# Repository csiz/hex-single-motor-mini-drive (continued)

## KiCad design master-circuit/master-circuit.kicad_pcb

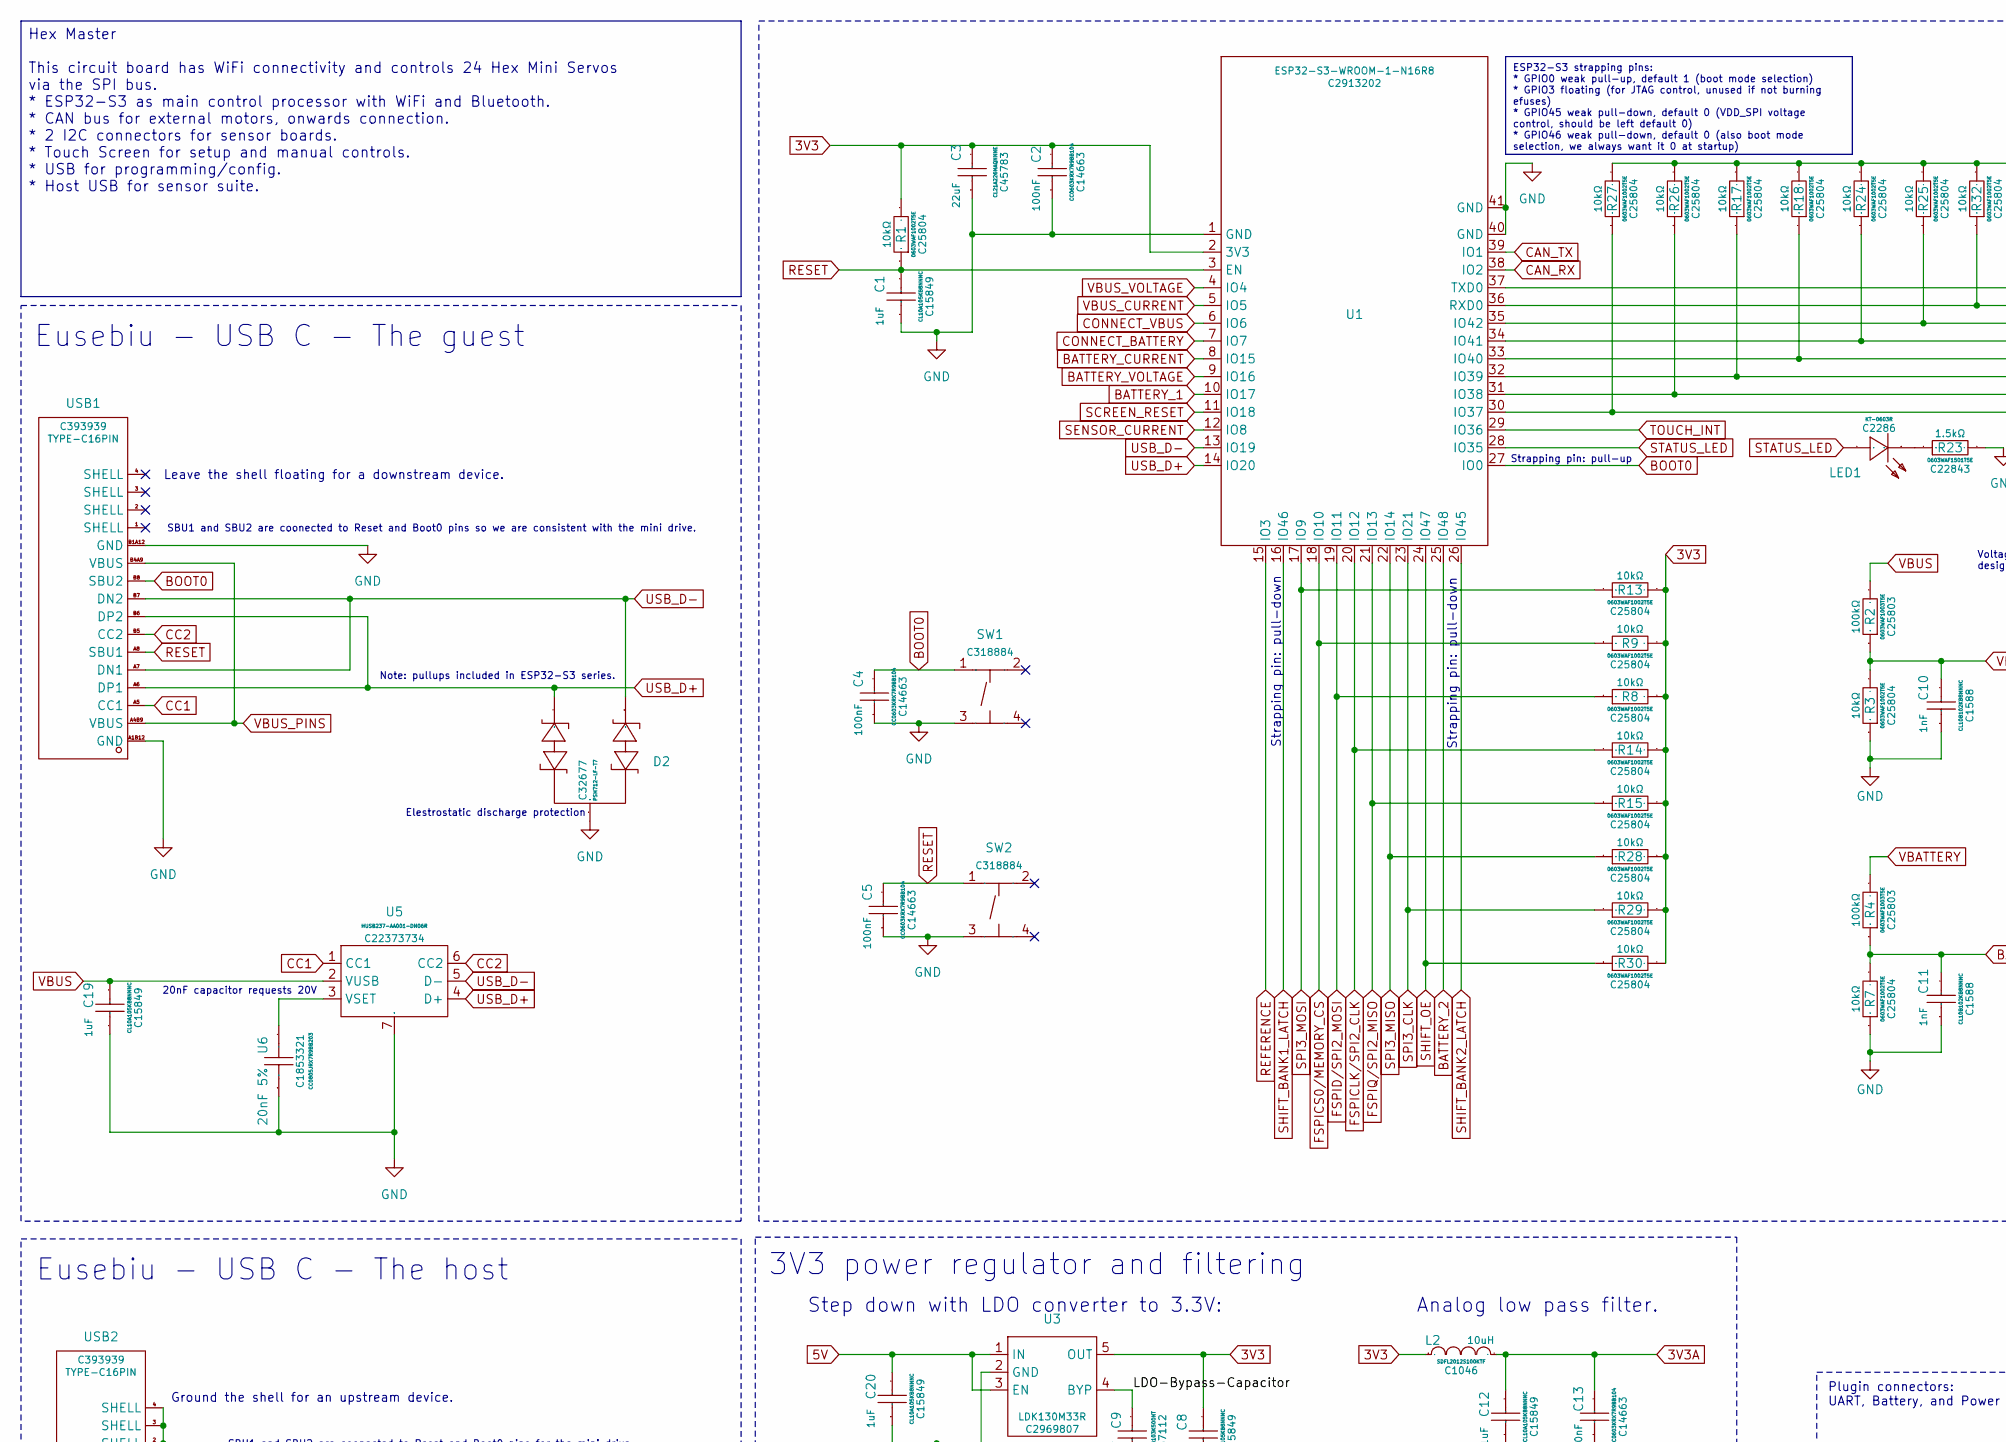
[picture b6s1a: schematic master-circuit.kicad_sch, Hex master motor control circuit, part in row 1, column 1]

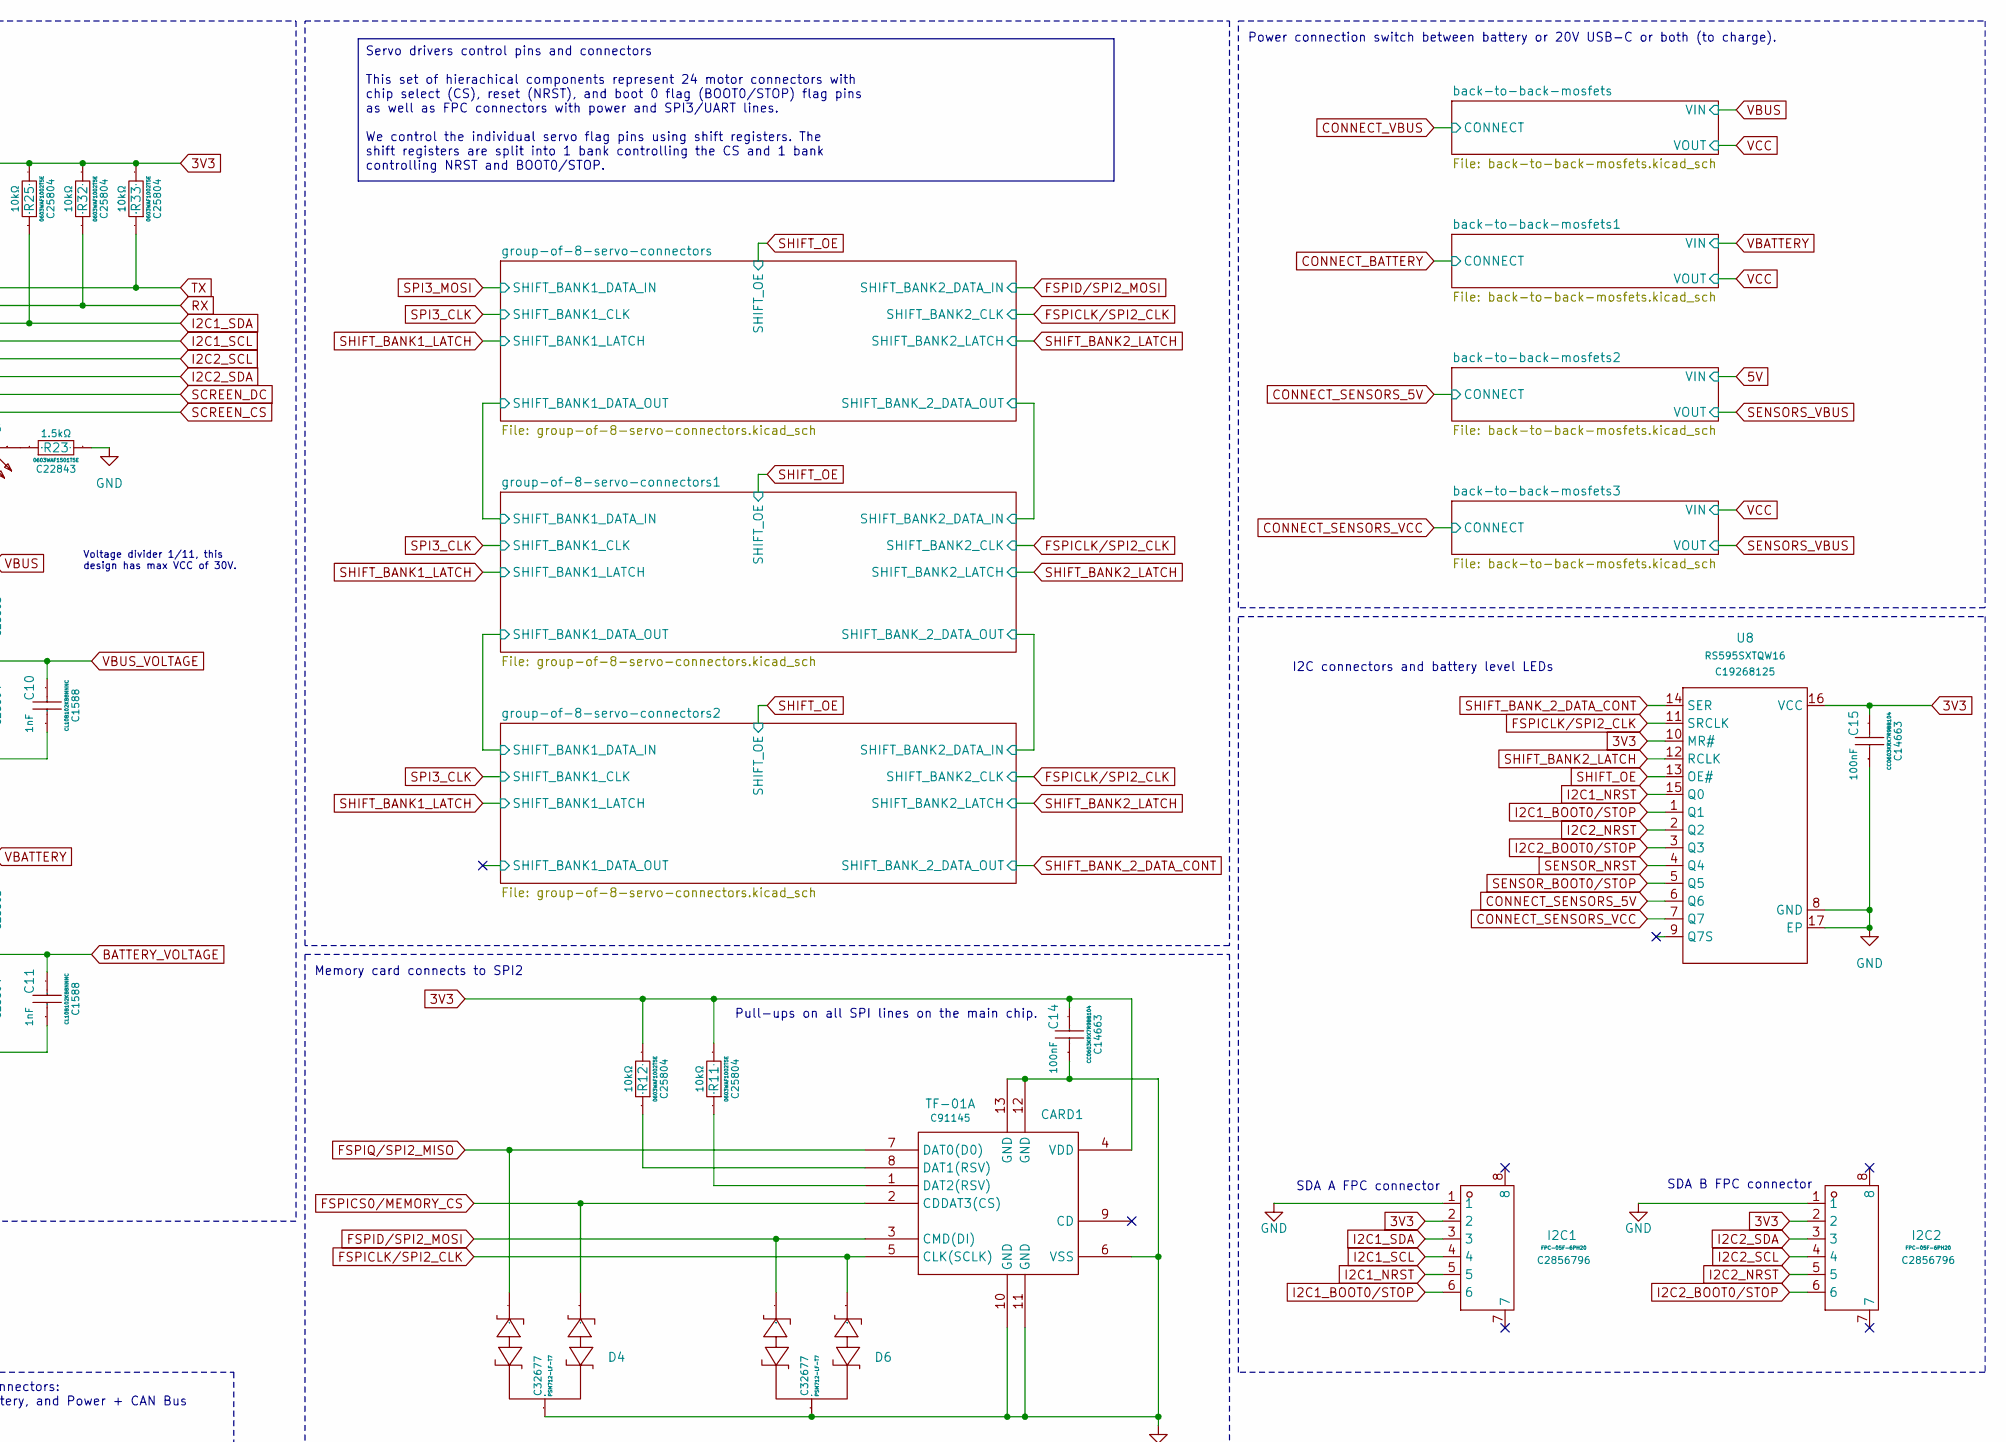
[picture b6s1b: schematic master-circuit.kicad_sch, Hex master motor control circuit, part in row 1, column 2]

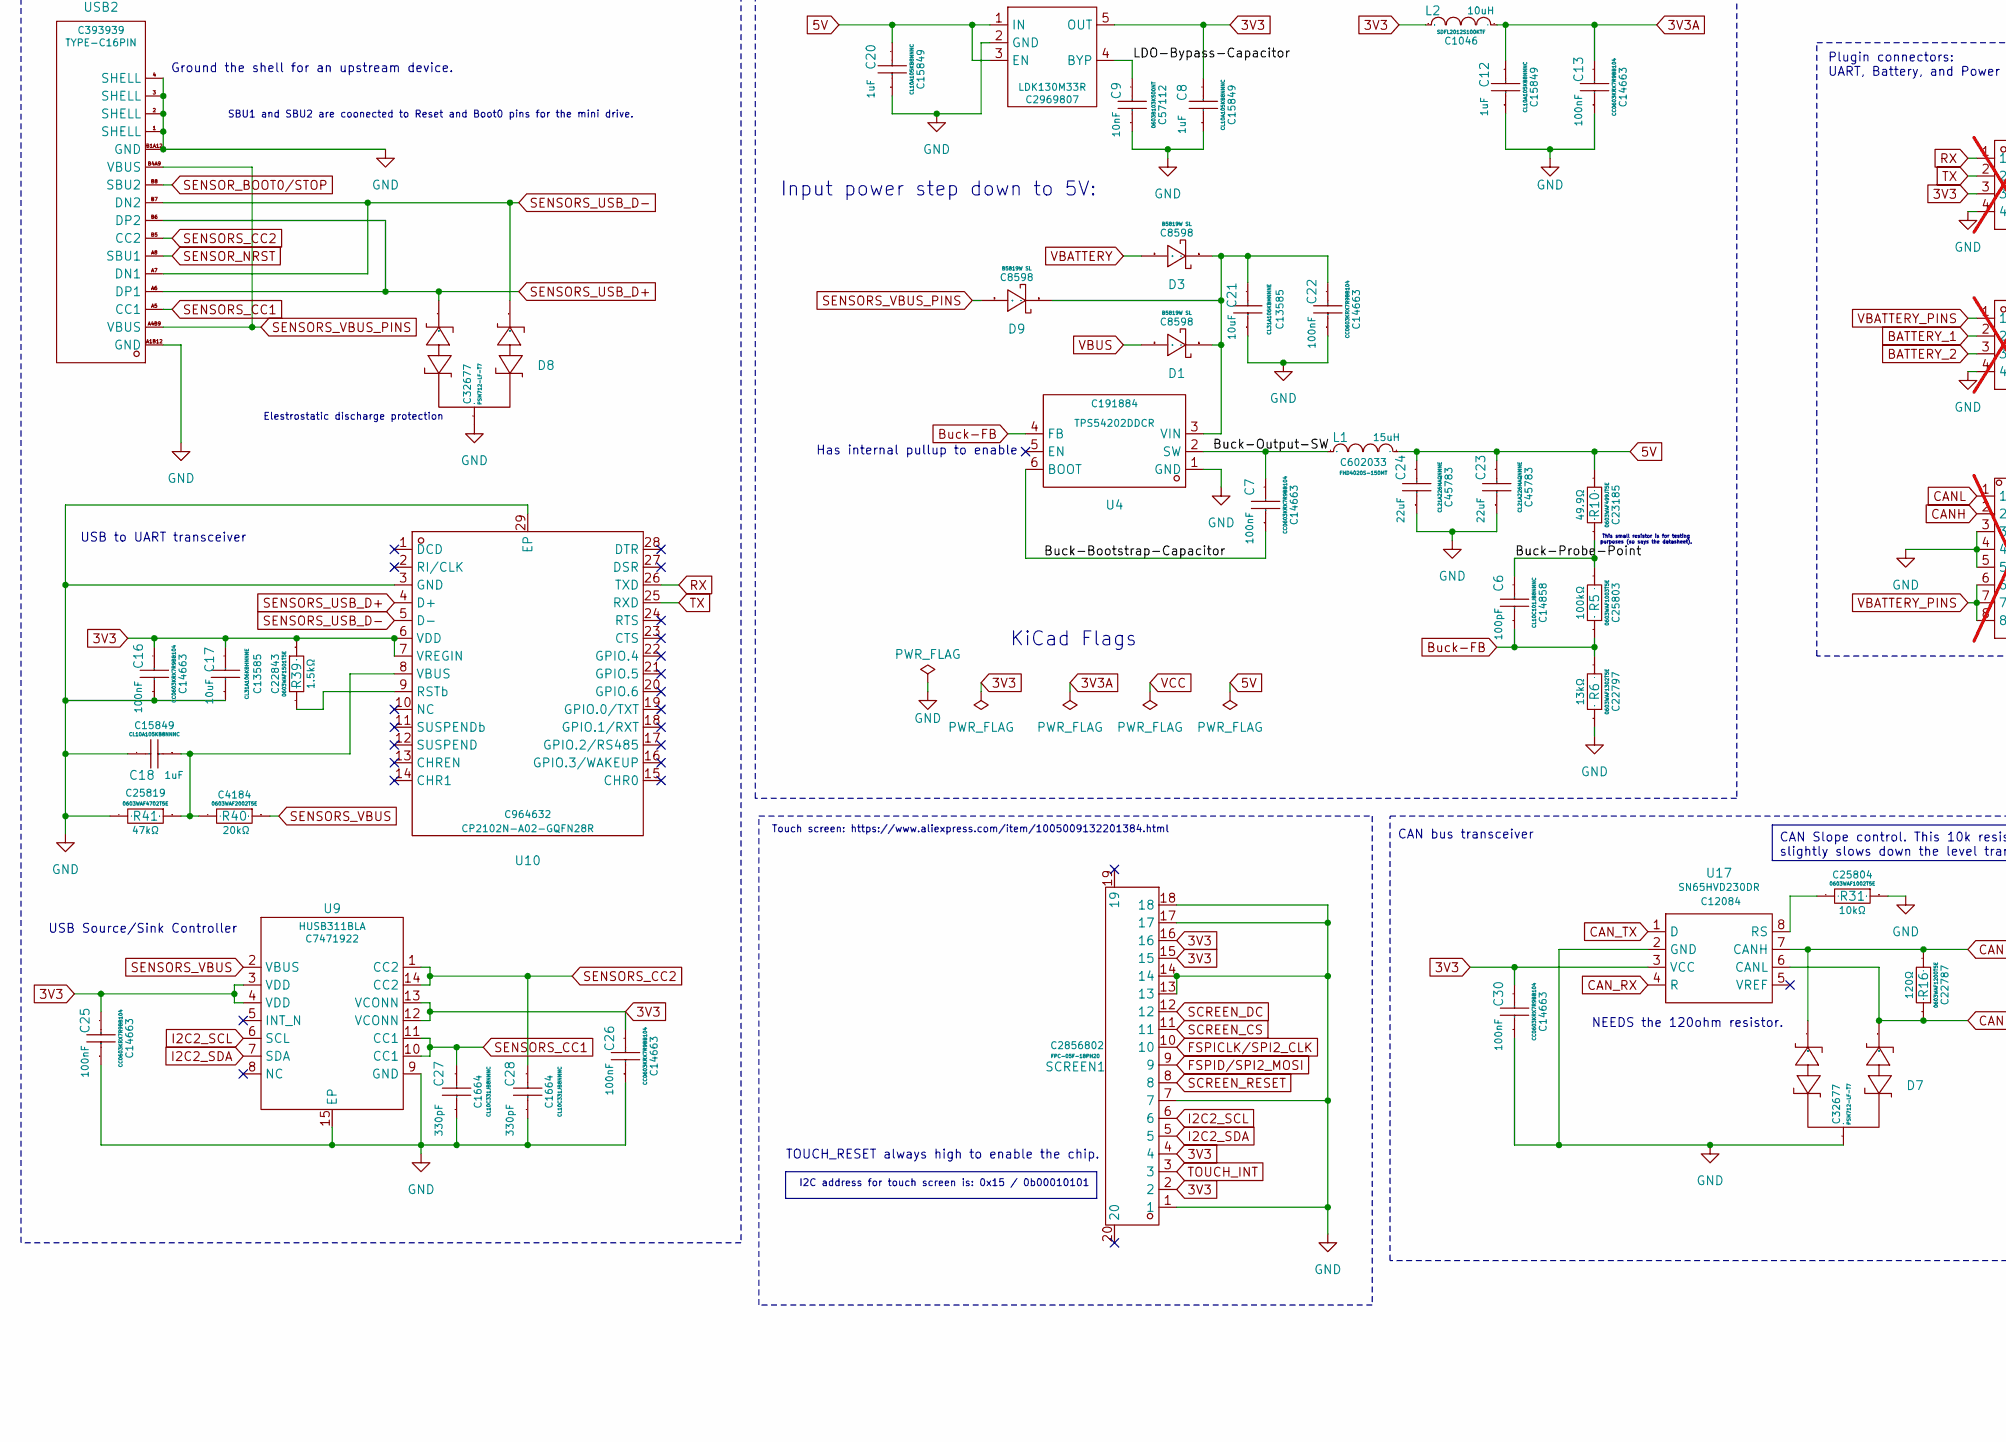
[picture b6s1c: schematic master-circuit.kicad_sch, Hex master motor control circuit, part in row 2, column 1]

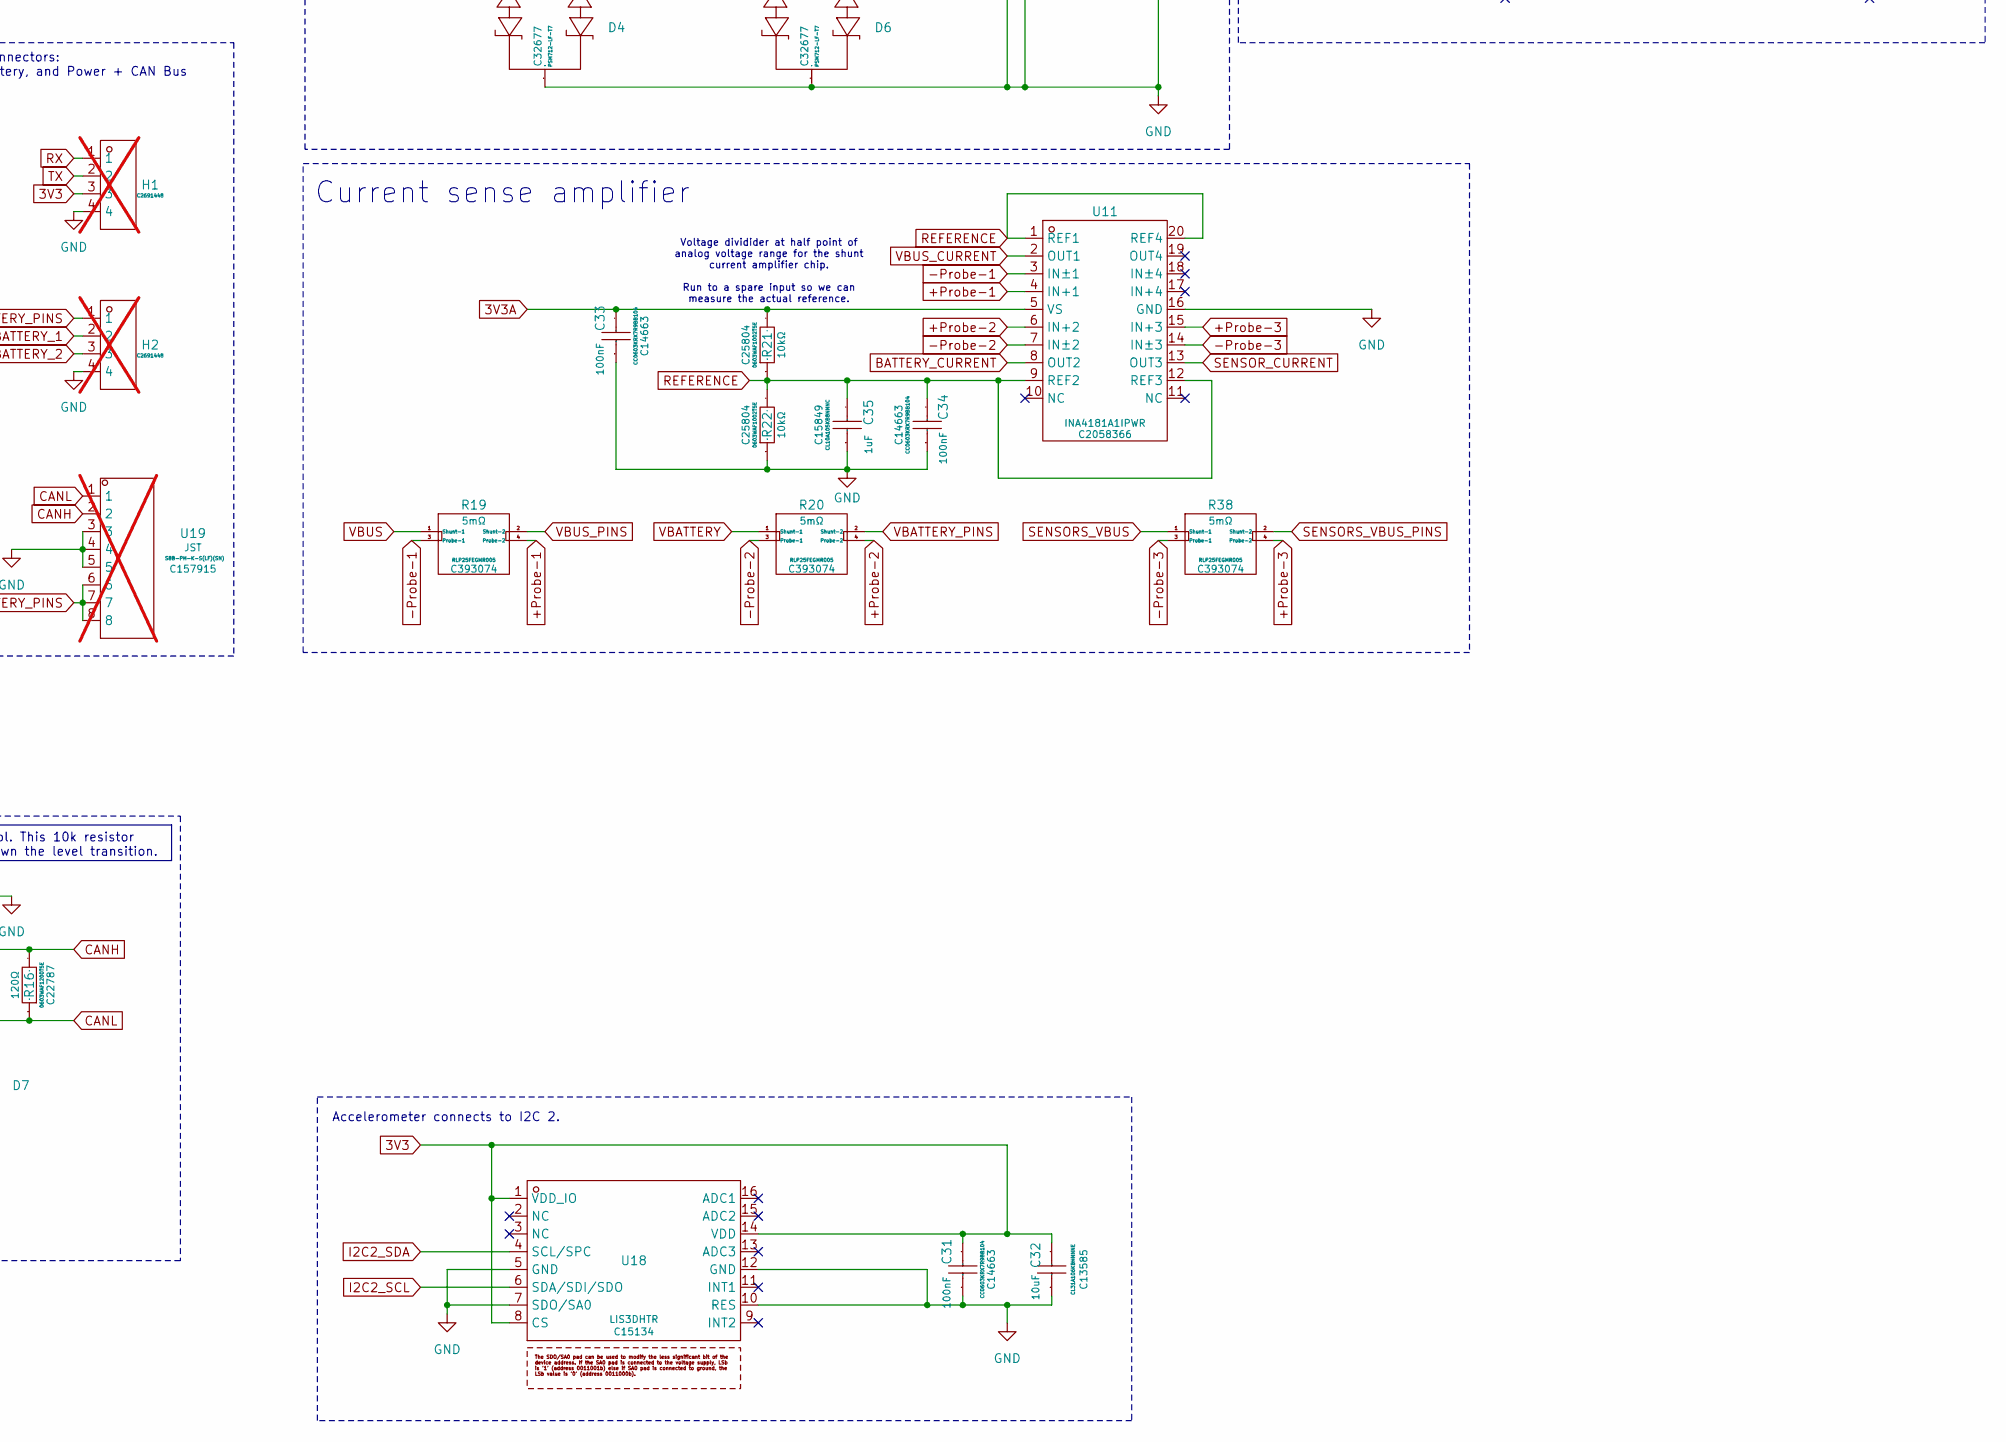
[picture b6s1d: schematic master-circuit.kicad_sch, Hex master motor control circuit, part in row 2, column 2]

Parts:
C1, C8, C12, C18, C19, C20, C35: 1uF; C0603; Manufacturer Part CL10A105KB8NNNC; LCSC Part Name 1uF ±10% 50V
C2, C4, C5, C7, C13, C14, C15, C16, C22, C25, C26, C30, C31, C33, C34: 100nF; C0603; Manufacturer Part CC0603KRX7R9BB104; LCSC Part Name 100nF ±10% 50V
C3, C23, C24: 22uF; C0805; Manufacturer Part CL21A226MAQNNNE; LCSC Part Name 22uF ±20% 25V
C6: 100pF; C0603; Manufacturer Part CL10C101JB8NNNC; LCSC Part Name 100pF ±5% 50V
C9: 10nF; C0603; Manufacturer Part 0603B103K500NT; LCSC Part Name 10nF ±10% 50V
C10, C11: 1nF; C0603; Manufacturer Part CL10B102KB8NNNC; LCSC Part Name 1nF ±10% 50V
C17, C21, C32: 10uF; C1206; Manufacturer Part CL31A106KBHNNNE; LCSC Part Name 10uF ±10% 50V
C27, C28: 330pF; C0603; Manufacturer Part CL10C331JB8NNNC; LCSC Part Name 330pF ±5% 50V
CARD1: TF-SMD_TF-01A; Manufacturer Part TF-01A; LCSC Part Name 自弹式 MicroSD卡(TF卡) 卡座
D1, D3, D9: SOD-123_L2.7-W1.6-LS3.7-RD-1; Manufacturer Part B5819W SL; LCSC Part Name 电压:40V 电流:1A
D2, D4, D6, D7, D8: SOT-23-3_L3.0-W1.7-P0.95-LS2.9-BR; Manufacturer Part PSM712-LF-T7; LCSC Part Name 单向TVS 12V截止 峰值浪涌电流：34A@8/20us 30A@8/20us
H1, H2: HDR-TH_4P-P2.54-V-M; Manufacturer Part PZ254V-11-04P; LCSC Part Name 1x4P 间距:2.54mm 方针 直插; not fitted
I2C1, I2C2: FPC-SMD_6P-P0.50_XUNPU_FPC-05F-6PH20; Manufacturer Part FPC-05F-6PH20; LCSC Part Name 翻盖式 卧贴 P数:6P 间距:0.5mm
L1: 15uH; IND-SMD_L4.0-W4.0; Manufacturer Part FHD4020S-150MT; LCSC Part Name 15uH ±20% 2.8A
L2: 10uH; L0805; Manufacturer Part SDFL2012S100KTF; LCSC Part Name 10uH ±10%
LED1: LED0603-RD; Manufacturer Part KT-0603R; LCSC Part Name 0603 红灯 高亮
R1, R3, R7, R8, R9, R11, R12, R13, R14, R15, R17, R18, R21, R22, R24, R25, R26, R27, R28, R29, R30, R31, R32, R33: 10kΩ; R0603; Manufacturer Part 0603WAF1002T5E; LCSC Part Name 厚膜电阻 10kΩ ±1% 100mW
R2, R4, R5: 100kΩ; R0603; Manufacturer Part 0603WAF1003T5E; LCSC Part Name 100kΩ ±1% 100mW 厚膜电阻
R6: 13kΩ; R0603; Manufacturer Part 0603WAF1302T5E; LCSC Part Name 13kΩ ±1% 100mW 厚膜电阻
R10: 49.9Ω; R0603; Manufacturer Part 0603WAF499JT5E; LCSC Part Name 49.9Ω ±1% 100mW 厚膜电阻
R16: 120Ω; R0603; Manufacturer Part 0603WAF1200T5E; LCSC Part Name 120Ω ±1% 100mW 厚膜电阻
R19, R20, R38: 5mΩ; R2512 Shunt with Kelvin connections; Manufacturer Part RLP25FEGMR005; LCSC Part Name 5mΩ ±1% 3W
R23, R39: 1.5kΩ; R0603; Manufacturer Part 0603WAF1501T5E; LCSC Part Name 1.5kΩ ±1% 100mW 厚膜电阻
R40: 20kΩ; R0603; Manufacturer Part 0603WAF2002T5E; LCSC Part Name 20kΩ ±1% 100mW 厚膜电阻
R41: 47kΩ; R0603; Manufacturer Part 0603WAF4702T5E; LCSC Part Name 47kΩ ±1% 100mW 厚膜电阻
SCREEN1: FPC-SMD_18P-P0.50_FPC-05F-18PH20; Manufacturer Part FPC-05F-18PH20; LCSC Part Name 翻盖式 卧贴 P数:18P 间距:0.5mm
SW1, SW2: SW-SMD_4P-L5.1-W5.1-P3.70-LS6.5-TL_H1.5; Manufacturer Part TS-1187A-B-A-B; LCSC Part Name 5.1*5.1*1.5mm 立贴 轻触开关
U1: WIRELM-SMD_ESP32-S3-WROOM-1; Manufacturer Part ESP32-S3-WROOM-1-N16R8; LCSC Part Name 通用型Wi-Fi+低功耗蓝牙MCU模组
U3: SOT-23-5_L3.0-W1.6-P0.95-LS2.8-BL; Manufacturer Part LDK130M33R; LCSC Part Name 300 mA低静态电流超低噪声LDO
U4: SOT-23-6_L2.9-W1.6-P0.95-LS2.8-BL; Manufacturer Part TPS54202DDCR; LCSC Part Name 4.5V至28V输入、2A输出、低EMI同步降压转换器
U5: TDFN-6_L2.0-W2.0-P0.65-TL-EP; Manufacturer Part HUSB237-AA001-DN06R; LCSC Part Name HUSB237-AA001-DN06R
U6: 20nF 5%; C0805; Manufacturer Part CC0805JRX7R9BB203; LCSC Part Name 20nF ±5% 50V
U8: DHVQFN-16_L3.5-W2.5-P0.50-BL-EP; Manufacturer Part RS595SXTQW16; LCSC Part Name 逻辑RS595S
U9: QFN-14_L2.5-W2.5-P0.50-TL-EP1.4; Manufacturer Part HUSB311BLA; LCSC Part Name HUSB311BLA
U10: QFN-28_L5.0-W5.0-P0.50-TL-EP3.3; Manufacturer Part CP2102N-A02-GQFN28R; LCSC Part Name CP2102N-A02-GQFN28R
U11: TSSOP-20_L6.5-W4.4-P0.65-LS6.4-BL; Manufacturer Part INA4181A1IPWR; LCSC Part Name INA4181A1IPWR
U17: SOIC-8_L4.9-W3.9-P1.27-LS6.0-BL; Manufacturer Part SN65HVD230DR; LCSC Part Name 3.3-V CAN 收发器
U18: LGA-16_L3.0-W3.0-P0.50-TL; Manufacturer Part LIS3DHTR; LCSC Part Name LIS3DHTR
U19: CONN-TH_S8B-PH-K-S-LF-SN; Manufacturer Part S8B-PH-K-S(LF)(SN); LCSC Part Name 1x8P 间距:2mm 弯插 系列:PH; not fitted
USB1, USB2: USB-C-SMD_TYPE-C16PIN; Manufacturer Part TYPE-C16PIN; LCSC Part Name Type-C 母 卧贴

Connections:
3V3: C2.2, C3.2, C8.2, C14.2, C15.2, C16.2, C17.2, C25.2, C26.2, C30.2, C31.2, C32.2, CARD1.4 (VDD), H1.3, I2C1.2, I2C2.2, L2.1, R1.2, R8.2, R9.2, R11.2, R12.2, R13.2, R14.2, R15.2, R17.2, R18.2, R24.2, R25.2, R26.2, R27.2, R28.2, R29.2, R30.2, R32.2, R33.2, R39.1, SCREEN1.2, SCREEN1.4, SCREEN1.15, SCREEN1.16, U1.2 (3V3), U3.5 (OUT), U8.10 (MR#), U8.16 (VCC), U9.3 (VDD), U9.4 (VDD), U9.12 (VCONN), U9.13 (VCONN), U10.6 (VDD), U10.7 (VREGIN), U17.3 (VCC), U18.1 (VDD_IO), U18.8 (CS), U18.14 (VDD); also elsewhere on the board
3V3A: C12.2, C13.2, C33.2, L2.2, R21.2, U11.5 (VS)
5V: C20.2, C23.2, C24.2, L1.2, R10.2, U3.1 (IN), U3.3 (EN); also elsewhere on the board
+Probe-1: R19.4 (Probe-2), U11.4 (IN+1)
+Probe-2: R20.4 (Probe-2), U11.6 (IN+2)
+Probe-3: R38.4 (Probe-2), U11.15 (IN+3)
-Probe-1: R19.3 (Probe-1), U11.3 (IN±1)
-Probe-2: R20.3 (Probe-1), U11.7 (IN±2)
-Probe-3: R38.3 (Probe-1), U11.14 (IN±3)
/Buck-Bootstrap-Capacitor: C7.1, U4.6 (BOOT)
/Buck-Output-SW: C7.2, L1.1, U4.2 (SW)
/Buck-Probe-Point: C6.2, R5.2, R10.1
/LDO-Bypass-Capacitor: C9.2, U3.4 (BYP)
BATTERY_1: H2.2, U1.10 (IO17)
BATTERY_2: H2.3, U1.25 (IO48)
BATTERY_CURRENT: U1.8 (IO15), U11.8 (OUT2)
BATTERY_VOLTAGE: C11.2, R4.1, R7.2, U1.9 (IO16)
BOOT0: C4.2, SW1.1 (A), U1.27 (IO0), USB1.B8 (SBU2)
Buck-FB: C6.1, R5.1, R6.2, U4.4 (FB)
CANH: D7.2 (A1), R16.2, U17.7 (CANH), U19.2
CANL: D7.1 (A1), R16.1, U17.6 (CANL), U19.1
CAN_RX: U1.38 (IO2), U17.4 (R)
CAN_TX: U1.39 (IO1), U17.1 (D)
CC1: U5.1 (CC1), USB1.A5 (CC1)
CC2: U5.6 (CC2), USB1.B5 (CC2)
CONNECT_BATTERY: U1.7 (IO7); also elsewhere on the board
CONNECT_SENSORS_5V: U8.6 (Q6); also elsewhere on the board
CONNECT_SENSORS_VCC: U8.7 (Q7); also elsewhere on the board
CONNECT_VBUS: U1.6 (IO6); also elsewhere on the board
FSPICLK/SPI2_CLK: CARD1.5 (CLK(SCLK)), D6.1 (A1), R14.1, SCREEN1.10, U1.20 (IO12), U8.11 (SRCLK); also elsewhere on the board
FSPICS0/MEMORY_CS: CARD1.2 (CDDAT3(CS)), D4.1 (A1), R9.1, U1.18 (IO10)
FSPID/SPI2_MOSI: CARD1.3 (CMD(DI)), D6.2 (A1), R8.1, SCREEN1.9, U1.19 (IO11); also elsewhere on the board
FSPIQ/SPI2_MISO: CARD1.7 (DAT0(D0)), D4.2 (A1), R15.1, U1.21 (IO13)
GND: C1.1, C2.1, C3.1, C4.1, C5.1, C8.1, C9.1, C10.1, C11.1, C12.1, C13.1, C14.1, C15.1, C16.1, C17.1, C18.2, C19.1, C20.1, C21.1, C22.1, C23.1, C24.1, C25.1, C26.1, C27.1, C28.1, C30.1, C31.1, C32.1, C33.1, C34.1, C35.1, CARD1.6 (VSS), CARD1.10 (GND), CARD1.11 (GND), CARD1.12 (GND), CARD1.13 (GND), D2.3 (K), D4.3 (K), D6.3 (K), D7.3 (K), D8.3 (K), H1.4, H2.4, I2C1.1, I2C2.1, R3.1, R6.1, R7.1, R22.1, R23.2, R31.1, R41.2, SCREEN1.1, SCREEN1.7, SCREEN1.13, SCREEN1.14, SCREEN1.17, SCREEN1.18, SW1.3 (C), SW2.3 (C), U1.1 (GND), U1.40 (GND), U1.41 (GND), U3.2 (GND), U4.1 (GND), U5.7 (GND), U6.1, U8.8 (GND), U8.17 (EP), U9.9 (GND), U9.15 (EP), U10.3 (GND), U10.29 (EP), U11.16 (GND), U17.2 (GND), U18.5 (GND), U18.7 (SDO/SA0), U18.10 (RES), U18.12 (GND), U19.3, U19.4, U19.5, USB1.A1B12 (GND), USB1.B1A12 (GND), USB2.1 (SHELL), USB2.2 (SHELL), USB2.3 (SHELL), USB2.4 (SHELL), USB2.A1B12 (GND), USB2.B1A12 (GND); also elsewhere on the board
I2C1_BOOT0/STOP: I2C1.6, U8.1 (Q1)
I2C1_NRST: I2C1.5, U8.15 (Q0)
I2C1_SCL: I2C1.4, R24.1, U1.34 (IO41)
I2C1_SDA: I2C1.3, R25.1, U1.35 (IO42)
I2C2_BOOT0/STOP: I2C2.6, U8.3 (Q3)
I2C2_NRST: I2C2.5, U8.2 (Q2)
I2C2_SCL: I2C2.4, R18.1, SCREEN1.6, U1.33 (IO40), U9.6 (SCL), U18.6 (SDA/SDI/SDO)
I2C2_SDA: I2C2.3, R17.1, SCREEN1.5, U1.32 (IO39), U9.7 (SDA), U18.4 (SCL/SPC)
unnamed: CARD1.8 (DAT1(RSV)), R12.1
unnamed: CARD1.1 (DAT2(RSV)), R11.1
unnamed: C21.2, C22.2, D1.1 (-), D3.1 (-), D9.1 (-), U4.3 (VIN)
unnamed: LED1.1 (K), R23.1
unnamed: U5.3 (VSET), U6.2
unnamed: R39.2, U10.9 (RSTb)
unnamed: C18.1, R40.2, R41.1, U10.8 (VBUS)
unnamed: R31.2, U17.8 (RS)
REFERENCE: C34.2, C35.2, R21.1, R22.2, U1.15 (IO3), U11.1 (REF1), U11.9 (REF2), U11.12 (REF3), U11.20 (REF4)
RESET: C1.2, C5.2, R1.1, SW2.1 (A), U1.3 (EN), USB1.A8 (SBU1)
RX: H1.1, R32.1, U1.36 (RXD0), U10.26 (TXD); also elsewhere on the board
SCREEN_CS: R27.1, SCREEN1.11, U1.30 (IO37)
SCREEN_DC: R26.1, SCREEN1.12, U1.31 (IO38)
SCREEN_RESET: SCREEN1.8, U1.11 (IO18)
SENSORS_CC1: C27.2, U9.10 (CC1), U9.11 (CC1), USB2.A5 (CC1)
SENSORS_CC2: C28.2, U9.1 (CC2), U9.14 (CC2), USB2.B5 (CC2)
SENSORS_USB_D+: D8.2 (A1), U10.4 (D+), USB2.A6 (DP1), USB2.B6 (DP2)
SENSORS_USB_D-: D8.1 (A1), U10.5 (D-), USB2.A7 (DN1), USB2.B7 (DN2)
SENSORS_VBUS: R38.1 (Shunt-1), R40.1, U9.2 (VBUS); also elsewhere on the board
SENSORS_VBUS_PINS: D9.2 (+), R38.2 (Shunt-2), USB2.A4B9 (VBUS), USB2.B4A9 (VBUS)
SENSOR_BOOT0/STOP: U8.5 (Q5), USB2.B8 (SBU2)
SENSOR_CURRENT: U1.12 (IO8), U11.13 (OUT3)
SENSOR_NRST: U8.4 (Q4), USB2.A8 (SBU1)
SHIFT_BANK1_LATCH: U1.16 (IO46); also elsewhere on the board
SHIFT_BANK2_LATCH: U1.26 (IO45), U8.12 (RCLK); also elsewhere on the board
SHIFT_BANK_2_DATA_CONT: U8.14 (SER); also elsewhere on the board
SHIFT_OE: R30.1, U1.24 (IO47), U8.13 (OE#); also elsewhere on the board
SPI3_CLK: R29.1, U1.23 (IO21); also elsewhere on the board
SPI3_MISO: R28.1, U1.22 (IO14); also elsewhere on the board
SPI3_MOSI: R13.1, U1.17 (IO9); also elsewhere on the board
STATUS_LED: LED1.2 (A), U1.28 (IO35)
TOUCH_INT: SCREEN1.3, U1.29 (IO36)
TX: H1.2, R33.1, U1.37 (TXD0), U10.25 (RXD); also elsewhere on the board
USB_D+: D2.2 (A1), U1.14 (IO20), U5.4 (D+), USB1.A6 (DP1), USB1.B6 (DP2)
USB_D-: D2.1 (A1), U1.13 (IO19), U5.5 (D-), USB1.A7 (DN1), USB1.B7 (DN2)
VBATTERY: D3.2 (+), R4.2, R20.1 (Shunt-1); also elsewhere on the board
VBATTERY_PINS: H2.1, R20.2 (Shunt-2), U19.6, U19.7, U19.8
VBUS: C19.2, D1.2 (+), R2.2, R19.1 (Shunt-1), U5.2 (VUSB); also elsewhere on the board
VBUS_CURRENT: U1.5 (IO5), U11.2 (OUT1)
VBUS_PINS: R19.2 (Shunt-2), USB1.A4B9 (VBUS), USB1.B4A9 (VBUS)
VBUS_VOLTAGE: C10.2, R2.1, R3.2, U1.4 (IO4)

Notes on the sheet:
Power connection switch between battery or 20V USB-C or both (to charge).
Memory card connects to SPI2
NEEDS the 120ohm resistor.
SBU1 and SBU2 are coonected to Reset and Boot0 pins for the mini drive.
CAN bus transceiver
Strapping pin: pull-down
SDA A FPC connector
Has internal pullup to enable
Eusebiu - USB C - The guest
Plugin connectors: UART, Battery, and Power + CAN Bus
Analog low pass filter.
Elestrostatic discharge protection
I2C connectors and battery level LEDs
This small resistor is for testing purposes (so says the datasheet).
Accelerometer connects to I2C 2.
Eusebiu - USB C - The host
Current sense amplifier
Voltage divider 1/11, this design has max VCC of 30V.
Note: pullups included in ESP32-S3 series.
Leave the shell floating for a downstream device.
Step down with LDO converter to 3.3V:
SDA B FPC connector
KiCad Flags
SBU1 and SBU2 are coonected to Reset and Boot0 pins so we are consistent with the mini drive.
Pull-ups on all SPI lines on the main chip.
Ground the shell for an upstream device.
20nF capacitor requests 20V
Voltage dividider at half point of analog voltage range for the shunt current amplifier chip. Run to a spare input so we can measure the actual reference.
Strapping pin: pull-up
Input power step down to 5V:
Touch screen: https://www.aliexpress.com/item/1005009132201384.html
USB Source/Sink Controller
3V3 power regulator and filtering
USB to UART transceiver
TOUCH_RESET always high to enable the chip.
ESP32-S3 strapping pins: * GPIO0 weak pull-up, default 1 (boot mode selection) * GPIO3 floating (for JTAG control, unused if not burning efuses) * GPIO45 weak pull-down, default 0 (VDD_SPI voltage control, should be left default 0) * GPIO46 weak pull-down, default 0 (also boot mode selection, we al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
Hex Master This circuit board has WiFi connectivity and controls 24 Hex Mini Servos via the SPI bus. * ESP32-S3 as main control processor with WiFi and Bluetooth. * CAN bus for external motors, onwards connection. * 2 I2C connectors for sensor boards. * Touch Screen for setup and manual controls. *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
CAN Slope control. This 10k resistor slightly slows down the level transition.
Servo drivers control pins and connectors This set of hierachical components represent 24 motor connectors with chip select (CS), reset (NRST), and boot 0 flag (BOOT0/STOP) flag pins as well as FPC connectors with power and SPI3/UART lines. We control the individual servo flag pins using shift regi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
I2C address for touch screen is: 0x15 / 0b00010101
